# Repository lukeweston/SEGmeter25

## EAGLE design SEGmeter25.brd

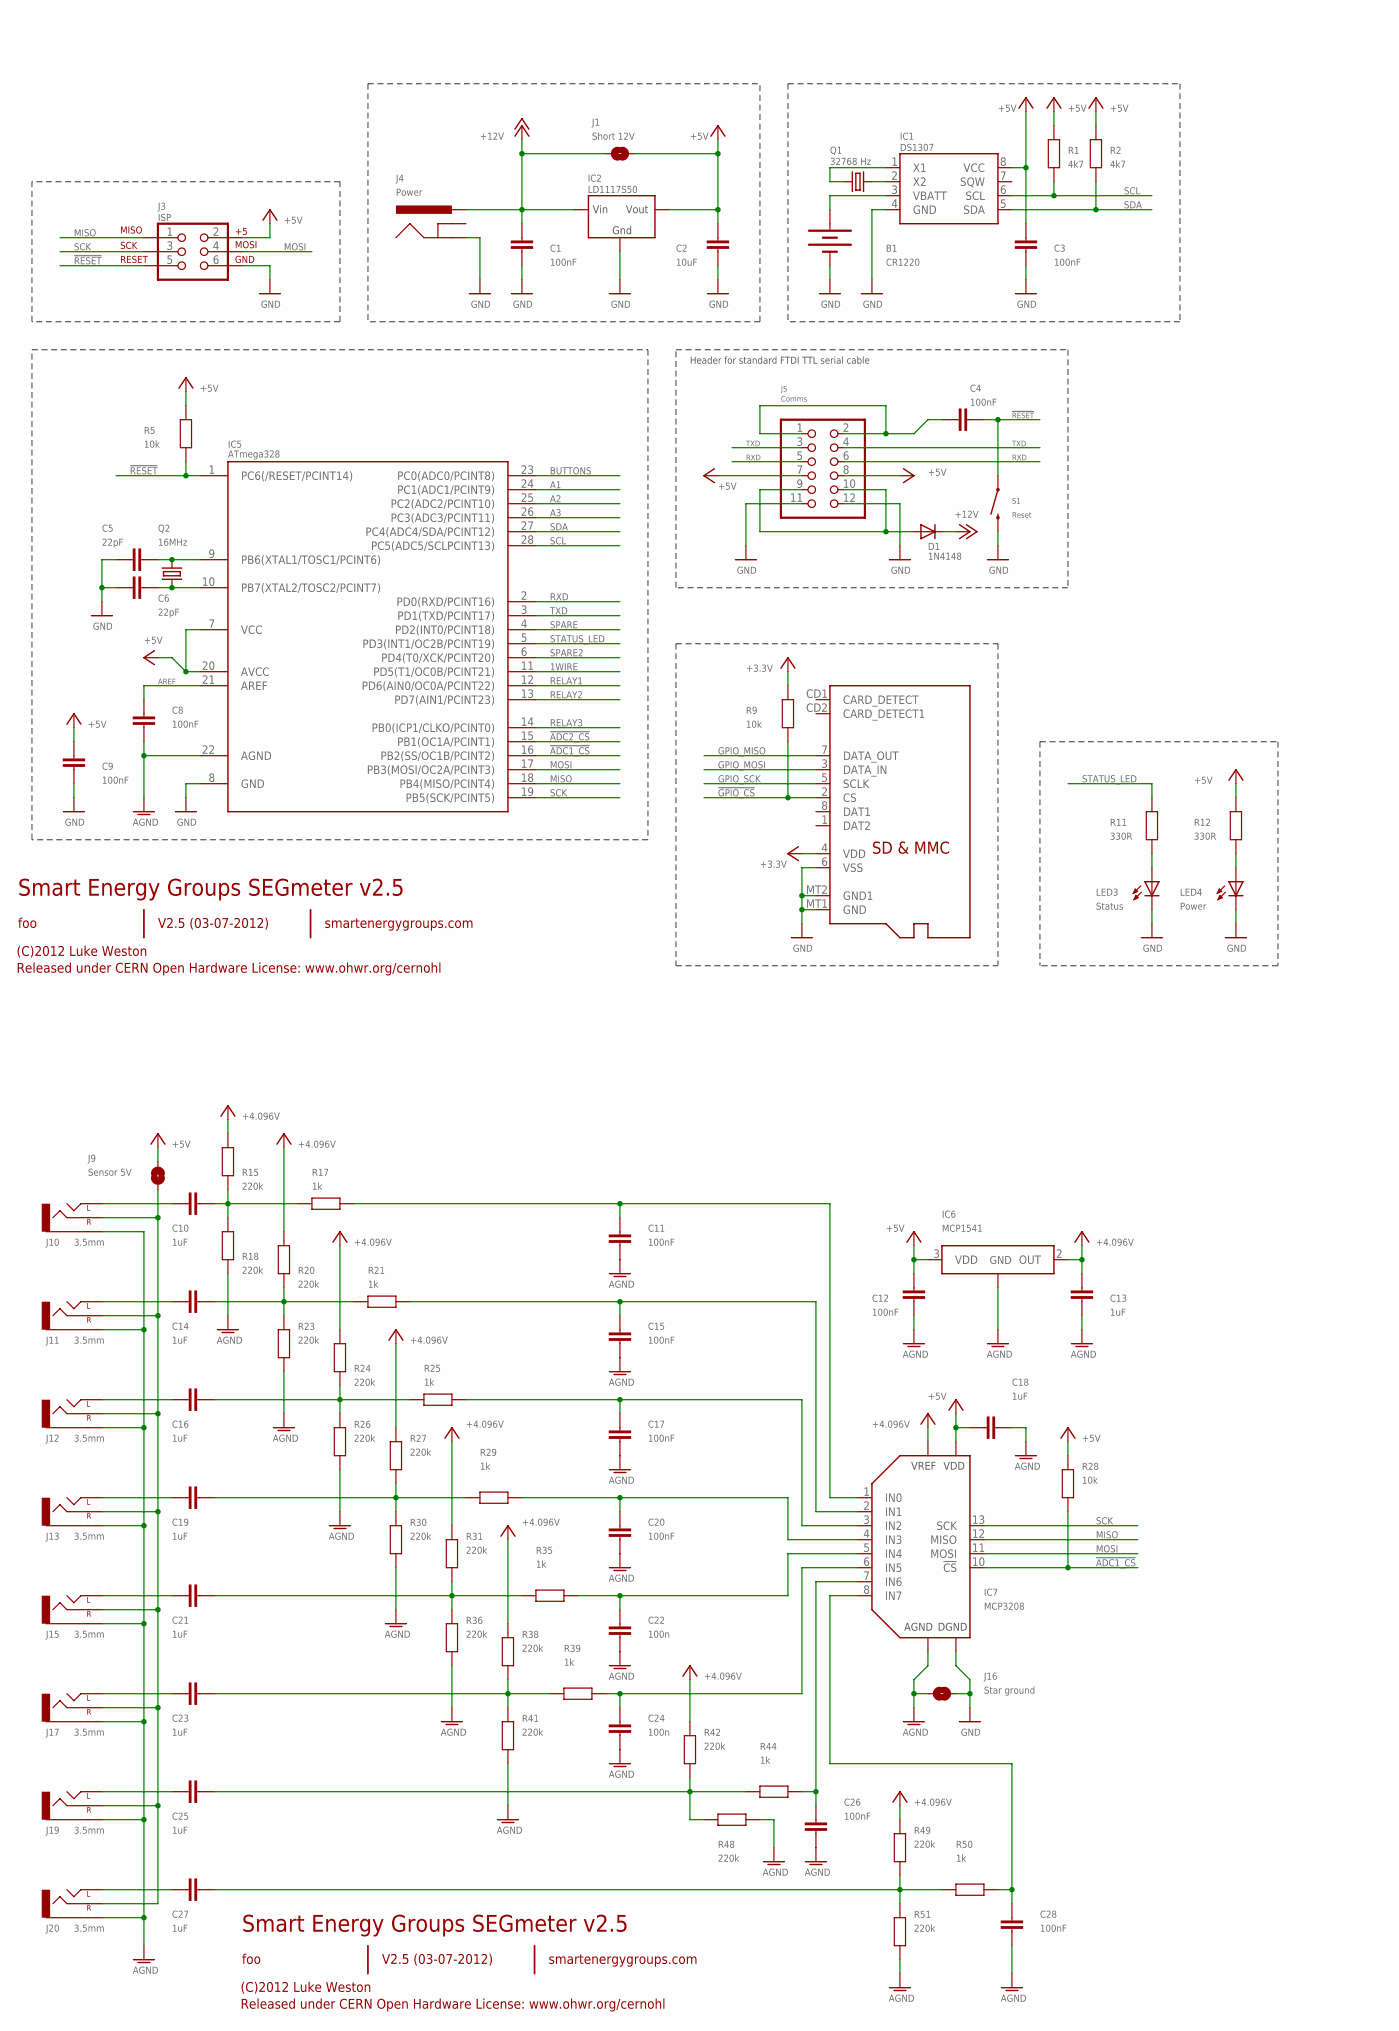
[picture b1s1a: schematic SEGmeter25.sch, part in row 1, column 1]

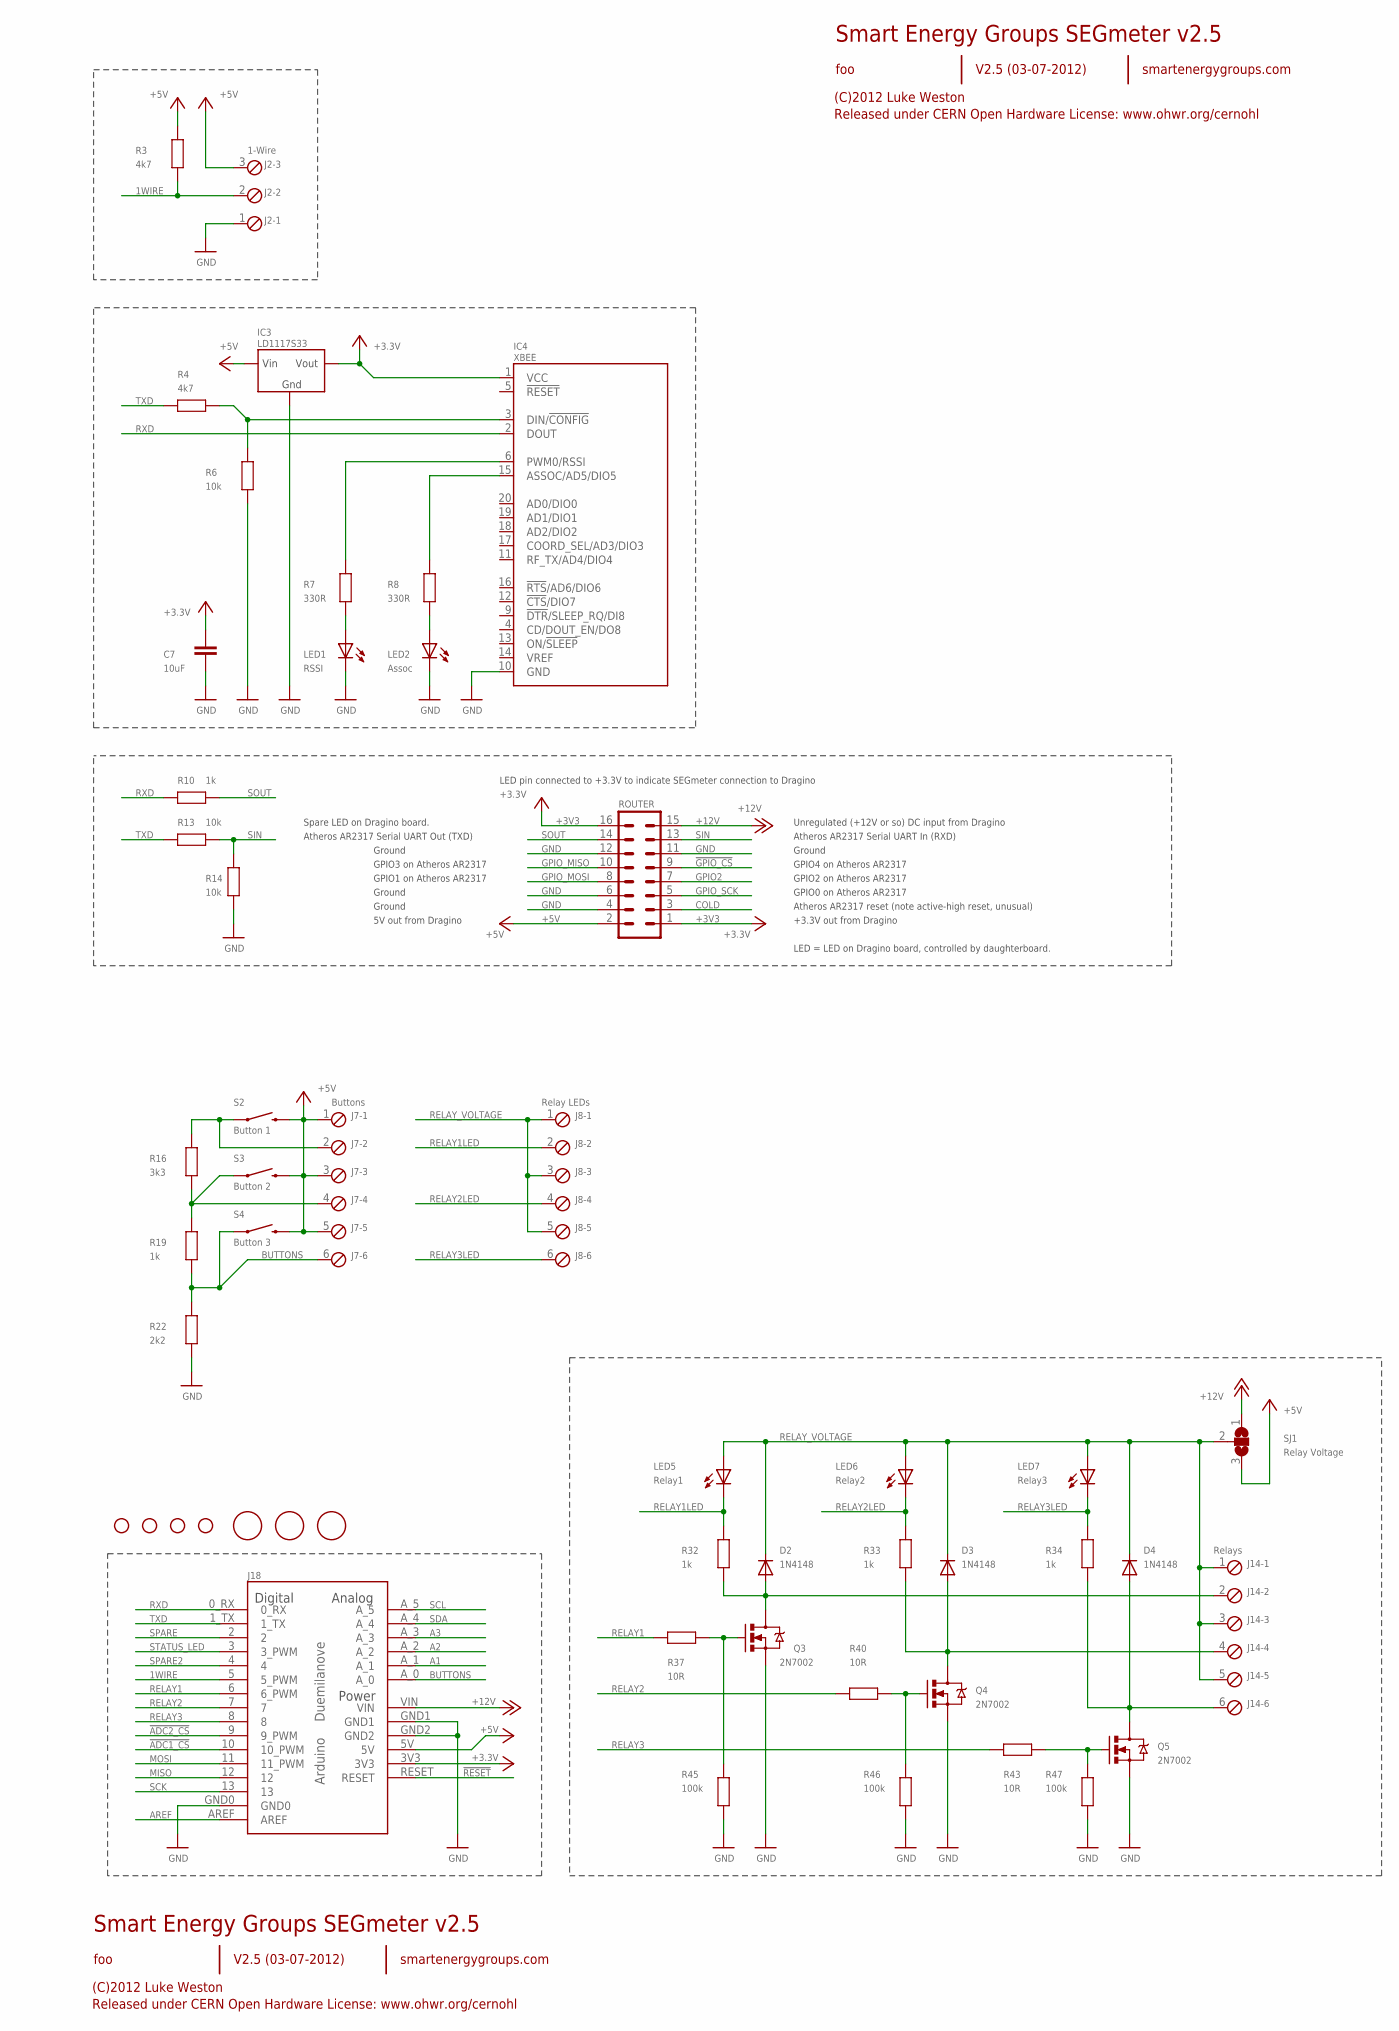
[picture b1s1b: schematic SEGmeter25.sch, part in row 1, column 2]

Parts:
B1: CR1220; BATTCON_12MM
C1, C3, C4, C8, C9, C11, C12, C15, C17, C20, C26, C28: 100nF; 0805
C2, C7: 10uF; 0805
C5, C6: 22pF; 0805
C10, C13, C14, C16, C18, C19, C21, C23, C25, C27: 1uF; 0805
C22, C24: 100n; 0805
D1, D2, D3, D4: 1N4148; SOD-323
FID1, FID2, FID3: FIDUCIAL; FIDUCIAL_1MM
H1, H2, H3, H4: STAND-OFF
IC1: DS1307; SO08
IC2: LD1117S50; SOT223
IC3: LD1117S33; SOT223
IC4: XBEE; XBEE-PRO
IC5: ATmega328; DIL28-3
IC6: MCP1541; TO92-STRAIGHT
IC7: MCP3208; DIL16
J1: Short 12V; SJ
J2: 1-Wire; 3POL254
J3: ISP; 2X3-NS
J4: Power; POWER_JACK_SLOT
J5: Comms; 2X06
J6: MICROSD
J7: Buttons; 6POL254
J8: Relay LEDs; 6POL254
J9: Sensor 5V; SJ
J10, J11, J12, J13, J15, J17, J19, J20: 3.5mm; AUDIO-JACK-3.5MM-SMD
J14: Relays; 6POL254
J16: Star ground; SJ
J18: Arduino-compatible headers; NO-OUTLINE-OCTAGONAL-NOTEXT
LED1: RSSI; LED-0805
LED2: Assoc; LED-0805
LED3: Status; LED-0805
LED4: Power; LED-0805
LED5: Relay1; LED-0805
LED6: Relay2; LED-0805
LED7: Relay3; LED-0805
Q1: 32768 Hz; CRYSTAL-32KHZ-SMD
Q2: 16MHz; CRYSTAL-SMD-5X3
Q3, Q4, Q5: 2N7002; SOT23-3
R1, R2, R3, R4: 4k7; 0805
R5, R6, R9, R13, R14, R28: 10k; 0805
R7, R8, R11, R12: 330R; 0805
R10, R17, R19, R21, R25, R29, R32, R33, R34, R35, R39, R44, R50: 1k; 0805
R15, R18, R20, R23, R24, R26, R27, R30, R31, R36, R38, R41, R42, R48, R49, R51: 220k; 0805
R16: 3k3; 0805
R22: 2k2; 0805
R37, R40, R43: 10R; 0805
R45, R46, R47: 100k; 0805
ROUTER: MA08-2
S1: Reset; TACTILE_SWITCH_SMD
S2: Button 1; TACTILE_SWITCH_SMD
S3: Button 2; TACTILE_SWITCH_SMD
S4: Button 3; TACTILE_SWITCH_SMD
SJ1: Relay Voltage; SJ_2

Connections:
1WIRE: IC5.11 (PD5(T1/OC0B/PCINT21)), J2.2, J18.5 (5_PWM), R3.1
3.3VTXD: IC4.3 (DIN/!CONFIG), R4.2, R6.1
!ADC1_CS: IC5.16 (PB2(SS/OC1B/PCINT2)), IC7.10 (!CS), J18.10 (10_PWM), R28.1
!ADC2_CS: IC5.15 (PB1(OC1A/PCINT1)), J18.9 (9_PWM)
!GPIO_CS: J6.2 (CS), R9.1, ROUTER.9
!RESET: C4.1, IC5.1 (PC6(/RESET/PCINT14)), J3.5, J18.RESET, R5.2, S1.1
+3V3: C7.2, IC3.2 (VOUT), IC4.1 (VCC), J6.4 (VDD), J18.3V3, R9.2, ROUTER.1, ROUTER.16
+5V: C2.2, C3.2, C9.2, C12.2, C18.2, IC1.8 (VCC), IC2.2 (VOUT), IC3.3 (VIN), IC5.7 (VCC), IC5.20 (AVCC), IC6.3 (VDD), IC7.16 (VDD), J1.2, J2.3, J3.2, J5.7, J5.8, J7.1, J7.3, J7.5, J9.2, J18.5V, R1.2, R2.2, R3.2, R5.1, R12.2, R28.2, ROUTER.2, S2.3 (2), S3.3 (2), S4.3 (2), SJ1.3
+12V: C1.2, D1.1 (C), IC2.3 (VIN), J1.1, J4.PWR, J18.VIN, ROUTER.15, SJ1.1
A1: IC5.24 (PC1(ADC1/PCINT9)), J18.A_1
A2: IC5.25 (PC2(ADC2/PCINT10)), J18.A_2
A3: IC5.26 (PC3(ADC3/PCINT11)), J18.A_3
AGND: C8.1, C11.1, C12.1, C13.1, C15.1, C17.1, C18.1, C20.1, C22.1, C24.1, C26.1, C28.1, IC5.22 (AGND), IC6.1 (GND), IC7.14 (AGND), J10.SLEEVE, J11.SLEEVE, J12.SLEEVE, J13.SLEEVE, J15.SLEEVE, J16.2, J17.SLEEVE, J19.SLEEVE, J20.SLEEVE, R18.1, R23.1, R26.1, R30.1, R36.1, R41.1, R48.1, R51.1
AREF: C8.2, IC5.21 (AREF), J18.AREF
BUTTON1: J7.2, R16.2, S2.1
BUTTON2: J7.4, R16.1, R19.2, S3.1
BUTTONS: IC5.23 (PC0(ADC0/PCINT8)), J7.6, J18.A_0, R19.1, R22.2, S4.1
COLD: ROUTER.3
GND: B1.GND (-), C1.1, C2.1, C3.1, C5.2, C6.2, C7.1, C9.1, IC1.4 (GND), IC2.1 (GND), IC3.1 (GND), IC4.10 (GND), IC5.8 (GND), IC7.9 (DGND), J2.1, J3.6, J4.GND, J5.11, J5.12, J6.6 (VSS), J6.MT1 (GND), J6.MT2 (GND1), J16.1, J18.GND0, J18.GND1, J18.GND2, LED1.C, LED2.C, LED3.C, LED4.C, Q3.2 (S), Q4.2 (S), Q5.2 (S), R6.2, R14.2, R22.1, R45.1, R46.1, R47.1, ROUTER.4, ROUTER.6, ROUTER.11, ROUTER.12, S1.3 (2)
GPIO2: ROUTER.7
GPIO_MISO: J6.7 (DATA_OUT), ROUTER.10
GPIO_MOSI: J6.3 (DATA_IN), ROUTER.8
GPIO_SCK: J6.5 (SCLK), ROUTER.5
MISO: IC5.18 (PB4(MISO/PCINT4)), IC7.12 (MISO), J3.1, J18.12
MOSI: IC5.17 (PB3(MOSI/OC2A/PCINT3)), IC7.11 (MOSI), J3.4, J18.11 (11_PWM)
unnamed: LED4.A, R12.1
unnamed: LED3.A, R11.1
unnamed: D1.2 (A), J5.9, J5.10
unnamed: IC4.6 (PWM0/RSSI), R7.1
unnamed: IC4.15 (ASSOC/AD5/DIO5), R8.1
unnamed: LED2.A, R8.2
unnamed: LED1.A, R7.2
unnamed: IC1.2 (X2), Q1.X2 (2)
unnamed: B1.PWR@1 (+), IC1.3 (VBATT)
unnamed: IC1.1 (X1), Q1.X1 (1)
unnamed: D2.2 (A), J14.2, Q3.3 (D), R32.1
unnamed: D3.2 (A), J14.4, Q4.3 (D), R33.1
unnamed: C5.1, IC5.9 (PB6(XTAL1/TOSC1/PCINT6)), Q2.1
unnamed: C6.1, IC5.10 (PB7(XTAL2/TOSC2/PCINT7)), Q2.3 (2)
unnamed: C27.1, J20.TIP (LEFT)
unnamed: D4.2 (A), J14.6, Q5.3 (D), R34.1
unnamed: C25.1, J19.TIP (LEFT)
unnamed: C10.1, J10.TIP (LEFT)
unnamed: C4.2, J5.1, J5.2
unnamed: C14.1, J11.TIP (LEFT)
unnamed: C23.1, J17.TIP (LEFT)
unnamed: J9.1, J10.RING (RIGHT), J11.RING (RIGHT), J12.RING (RIGHT), J13.RING (RIGHT), J15.RING (RIGHT), J17.RING (RIGHT), J19.RING (RIGHT), J20.RING (RIGHT)
unnamed: C21.1, J15.TIP (LEFT)
unnamed: C19.1, J13.TIP (LEFT)
unnamed: C16.1, J12.TIP (LEFT)
unnamed: C10.2, R15.1, R17.2, R18.2
unnamed: C27.2, R49.1, R50.2, R51.2
unnamed: C25.2, R42.1, R44.2, R48.2
unnamed: C23.2, R38.1, R39.2, R41.2
unnamed: C21.2, R31.1, R35.2, R36.2
unnamed: C14.2, R20.1, R21.2, R23.2
unnamed: C16.2, R24.1, R25.2, R26.2
unnamed: C19.2, R27.1, R29.2, R30.2
unnamed: C26.2, IC7.7 (IN6), R44.1
unnamed: C15.2, IC7.2 (IN1), R21.1
unnamed: C17.2, IC7.3 (IN2), R25.1
unnamed: C20.2, IC7.4 (IN3), R29.1
unnamed: C22.2, IC7.5 (IN4), R35.1
unnamed: C28.2, IC7.8 (IN7), R50.1
unnamed: Q5.1 (G), R43.1, R47.2
unnamed: C24.2, IC7.6 (IN5), R39.1
unnamed: Q3.1 (G), R37.1, R45.2
unnamed: Q4.1 (G), R40.1, R46.2
unnamed: C11.2, IC7.1 (IN0), R17.1
RELAY1: IC5.12 (PD6(AIN0/OC0A/PCINT22)), J18.6 (6_PWM), R37.2
RELAY1LED: J8.2, LED5.C, R32.2
RELAY2: IC5.13 (PD7(AIN1/PCINT23)), J18.7, R40.2
RELAY2LED: J8.4, LED6.C, R33.2
RELAY3: IC5.14 (PB0(ICP1/CLKO/PCINT0)), J18.8, R43.2
RELAY3LED: J8.6, LED7.C, R34.2
RELAY_VOLTAGE: D2.1 (C), D3.1 (C), D4.1 (C), J8.1, J8.3, J8.5, J14.1, J14.3, J14.5, LED5.A, LED6.A, LED7.A, SJ1.2
RXD: IC4.2 (DOUT), IC5.2 (PD0(RXD/PCINT16)), J5.5, J5.6, J18.0_RX, R10.2
SCK: IC5.19 (PB5(SCK/PCINT5)), IC7.13 (SCK), J3.3, J18.13
SCL: IC1.6 (SCL), IC5.28 (PC5(ADC5/SCLPCINT13)), J18.A_5, R1.1
SDA: IC1.5 (SDA), IC5.27 (PC4(ADC4/SDA/PCINT12)), J18.A_4, R2.1
SIN: R13.1, R14.1, ROUTER.13
SOUT: R10.1, ROUTER.14
SPARE: IC5.4 (PD2(INT0/PCINT18)), J18.2
SPARE2: IC5.6 (PD4(T0/XCK/PCINT20)), J18.4
STATUS_LED: IC5.5 (PD3(INT1/OC2B/PCINT19)), J18.3 (3_PWM), R11.2
TXD: IC5.3 (PD1(TXD/PCINT17)), J5.3, J5.4, J18.1_TX, R4.1, R13.2
V+: C13.2, IC6.2 (OUT), IC7.15 (VREF), R15.2, R20.2, R24.2, R27.2, R31.2, R38.2, R42.2, R49.2

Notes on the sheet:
Header for standard FTDI TTL serial cable
+3.3V out from Dragino
GPIO0 on Atheros AR2317
GPIO2 on Atheros AR2317
GPIO4 on Atheros AR2317
GPIO3 on Atheros AR2317
GPIO1 on Atheros AR2317
5V out from Dragino
Spare LED on Dragino board.
Atheros AR2317 Serial UART Out (TXD)
Atheros AR2317 Serial UART In (RXD)
Unregulated (+12V or so) DC input from Dragino
Atheros AR2317 reset (note active-high reset, unusual)
Ground
LED = LED on Dragino board, controlled by daughterboard.
LED pin connected to +3.3V to indicate SEGmeter connection to Dragino
Smart Energy Groups SEGmeter v2.5
V2.5 (03-07-2012)
foo
(C)2012 Luke Weston
Released under CERN Open Hardware License: www.ohwr.org/cernohl
smartenergygroups.com

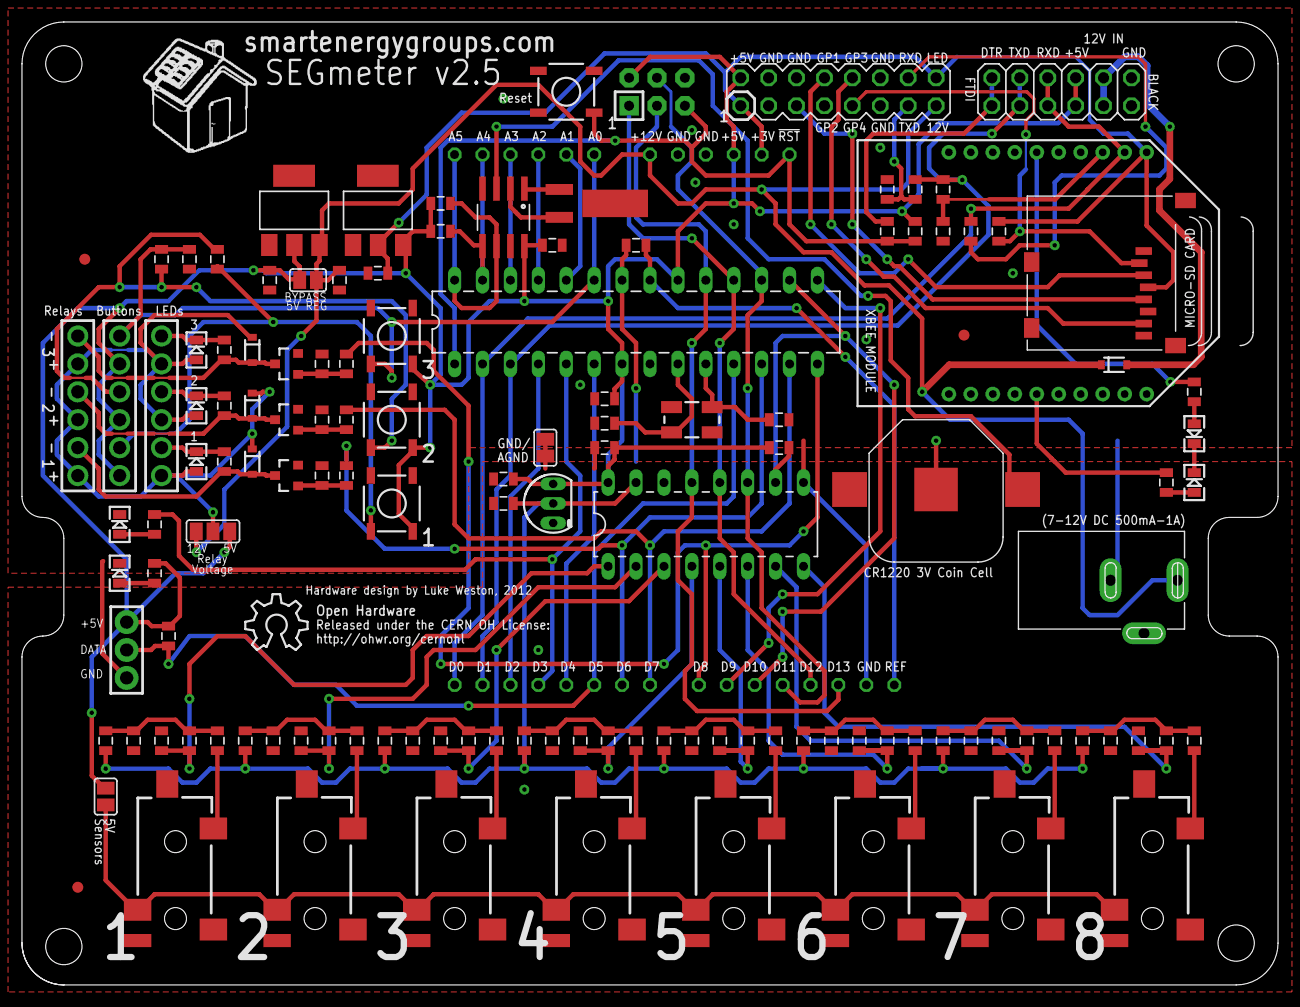
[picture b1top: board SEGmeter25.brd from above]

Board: 2 copper layers, 114.3 x 87.6 mm, 137 parts (0 on the bottom side), 85 nets.

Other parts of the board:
U$1: OSHW_8X200_NOTEXT

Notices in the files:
SEGmeter25.brd:
Released under the CERN OH License:
